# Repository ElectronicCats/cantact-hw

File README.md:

# CANtact Hardware

<p align="center">

</p>

<p align=center>
    Available at distributors:
 </p>
<p align=center>
  
</p>

<p align=center>

</p>

CANtact is a low-cost, open-source CAN bus interface hardware design, designed specifically for automotive diagnostics, industrial automation, and embedded systems development.

CANtact is a high-end CAN bus interface tool based on the original CANtact design, with optimization focused in rough order on (1) reliability, (2) ease of use, (3) cost-effectiveness, and finally (4) expandability. This results in a tool that covers many automotive and industrial use-cases, making it accessible for hobbyists and professionals alike.

As an open-source project and as a remix of the original CANtact design, it also collects inputs from various community members, and welcomes your contributions!

### FEATURES AVAILABLE ⚡🚗

* USB C, RJ45 and OBDII
* Low-cost design with open-source hardware files.
* 3D printable case files included.
* Compatible with popular CAN analysis software.
* Easy assembly with clear documentation.

## Thanks / Contributors

CANtact Hardware is a community-focused project, with major contributions from:

* Original CANtact design team
* ElectronicCats team (KiCad port, improvements, and variants)
* KiCad community for excellent open-source PCB design tools
* Open-source hardware community

### Useful References

If you don't know where to start with CAN bus communication, you may find automotive diagnostic resources and CAN bus protocol documentation useful.

You can see examples of CANtact being used in automotive diagnostics and industrial applications.

**WARNING**: Always ensure proper CAN bus termination and follow safety guidelines when working with automotive systems. Do NOT connect to live automotive systems without proper isolation.

## How to contribute 

Contributions are welcome!

Please read the document [**Contribution manual**](https://github.com/ElectronicCats/electroniccats-cla/blob/main/electroniccats-contribution-manual.md) which will show you how to contribute your changes to the project.

✨ Thanks to all our [Contributors](https://github.com/ElectronicCats/Minino/graphs/contributors)! ✨ ✨

See [**_Electronic Cats CLA_**](https://github.com/ElectronicCats/electroniccats-cla/blob/main/electroniccats-cla.md) for more information.

See the [**Community code of conduct**](https://github.com/ElectronicCats/electroniccats-cla/blob/main/electroniccats-community-code-of-conduct.md) for a vision of the community we want to build and what we expect from it.

## 3D Printed Case

Custom 3D printable case files are included in the `case/` directory:
- `CANTAC_case_top.stl` - Top cover
- `CANTAC_case_bttm.stl` - Bottom cover

## Documentation

- **Official Documentation**: [Linklayer Wiki](https://cantact.io/cantact/users-guide.html)

## Where to Buy

Ready-made CANtact devices are available from:

- 🇺🇸 [Hacker Warehouse](https://hackerwarehouse.com) (USA)

## License

This project CANtact Hardware is adapted from the original CANtact design and is licensed under CC BY-SA 4.0, "CANtact Hardware" contains modifications such as: porting the project to KiCad, modifying BOM and dimensions, and adding new variants, is licensed under CC BY-SA 4.0 by ElectronicCats.

Electronic Cats invests time and resources in providing this open-source design. Please support Electronic Cats and open-source hardware by purchasing products from Electronic Cats!

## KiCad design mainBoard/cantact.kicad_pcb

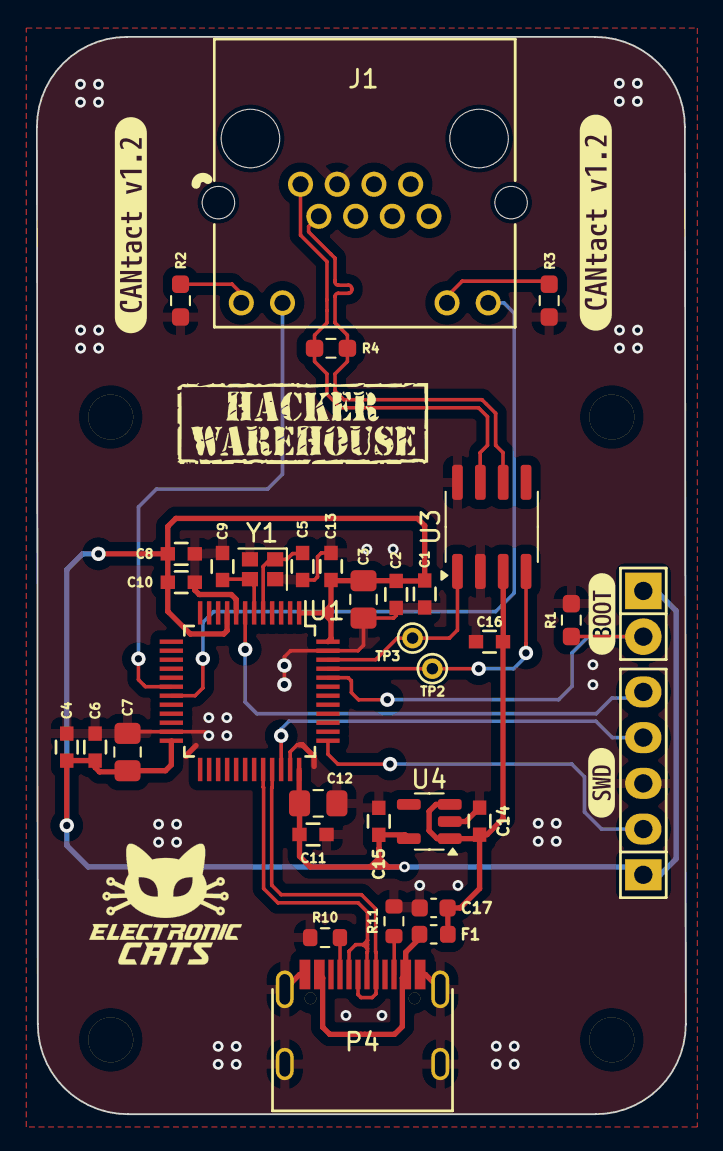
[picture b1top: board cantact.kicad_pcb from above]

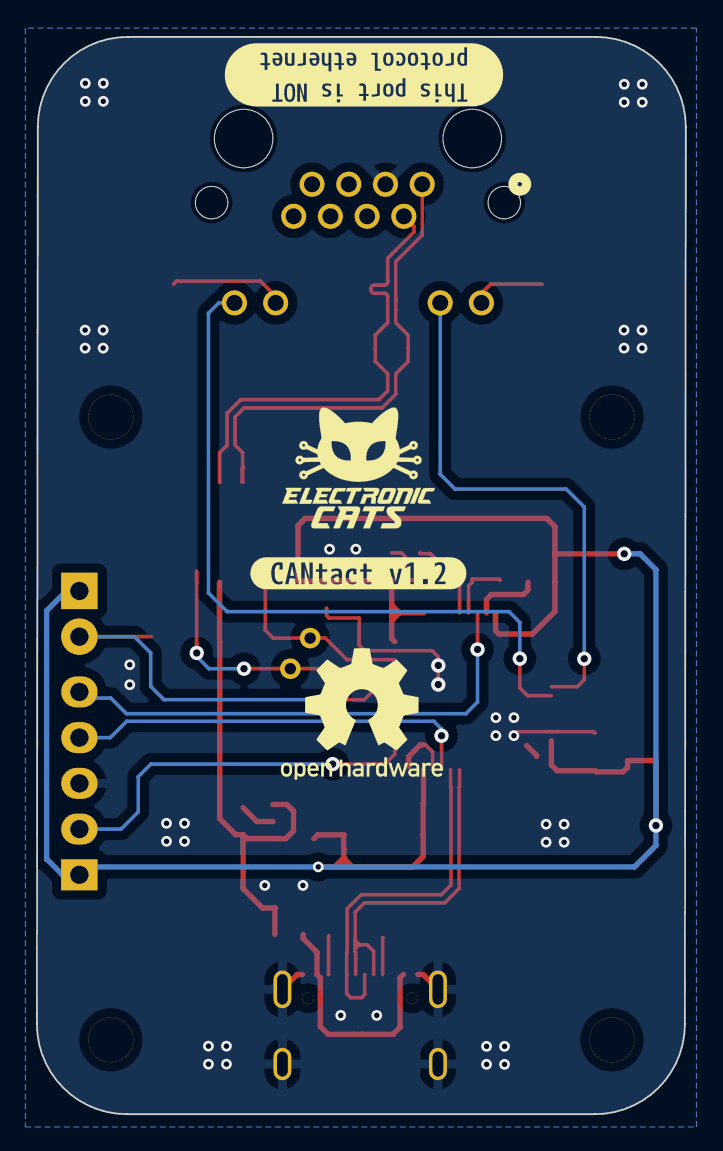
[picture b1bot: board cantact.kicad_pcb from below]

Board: 2 copper layers, 36.1 x 59.9 mm, 40 parts (2 on the bottom side), 22 nets.

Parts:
C1, C2, C4, C6, C11, C13, C16: 0.1uF; C_0603
C3, C7, C12: 4.7uF; C_0805_2012Metric_Pad1.18x1.45mm_HandSolder
C5, C9: 18pF; C_0603
C8: 10nF; C_0603
C10, C14, C15: 1uF; C_0603
C17: 10uF; C_0603_1608Metric
F1: 750mA; Fuse_0603_1608Metric
J1: Cantact; CONN12_R-RJ45_CKM
JP1: Boot Mode; Pin_Header_Straight_1x02
P2: SWD; Pin_Header_Straight_1x05
P4: USB_C_Plug_USB2.0; C393939
R1: 510; R_0603_1608Metric_Pad0.98x0.95mm_HandSolder
R2, R3, R4: 120; R_0603_1608Metric_Pad0.98x0.95mm_HandSolder
R10, R11: 5k1; R_0603_1608Metric
TP2, TP3: TST; PINTST
U1: STM32F042C6T6; LQFP-48_7x7mm_Pitch0.5mm
U3: MCP2551-I/SN; SOIC-8_3.9x4.9mm_P1.27mm
U4: XC6220B331MR-G; SOT-23-5
Y1: 16 Mhz; Crystal_SMD_2016-4Pin_2.0x1.6mm
kibuzzard-68FBEE71: G***; kibuzzard-68FBEE71
kibuzzard-68FBEEA6: G***; kibuzzard-68FBEEA6
kibuzzard-68FFF3A1: G***; kibuzzard-68FFF3A1
kibuzzard-68FFF3A9: G***; kibuzzard-68FFF3A9
kibuzzard-68FFF3B2: G***; kibuzzard-68FFF3B2
kibuzzard-68FFF13A: G***; kibuzzard-68FFF13A

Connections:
+3V3: C1.1, C2.1, C3.1, C4.1, C6.1, C7.1, C8.1, C10.1, C11.1, C12.1, C13.1, C15.1, JP1.1, P2.1, U1.1 (VBAT), U1.9 (VDDA), U1.24 (VDD), U1.36 (VDDIO), U1.48 (VDD), U4.5 (VOUT)
+5V: C14.1, C16.2, C17.1, F1.2, U3.3 (VDD), U4.1 (VIN), U4.3 (EN)
/CAN+: J1.1, R4.2, U3.7 (CANH)
/CAN-: J1.2, R4.1, U3.6 (CANL)
/CAN_RX: TP2.1, U1.45 (PB8), U3.4 (RXD)
/CAN_TX: TP3.1, U1.46 (PB9), U3.1 (TXD)
/D+: P4.A6 (D+), U1.33 (PA12)
/D-: P4.A7 (D-), U1.32 (PA11)
/LED_GREEN: J1.11, U1.18 (PB0)
/LED_RED: J1.9, U1.19 (PB1)
/NRST: P2.5, U1.7 (NRST)
/SWCLK: P2.2, U1.37 (PA14)
/SWDIO: P2.4, U1.34 (PA13)
GND: C1.2, C2.2, C3.2, C4.2, C5.2, C6.2, C7.2, C8.2, C9.2, C10.2, C11.2, C12.2, C13.2, C14.2, C15.2, C16.1, C17.2, J1.3, P2.3, P4.A1 (GND), P4.S1 (SHIELD), R1.2, R2.2, R3.2, R10.1, R11.1, U1.8 (VSSA), U1.23 (VSS), U1.35 (VSS), U1.47 (VSS), U3.2 (VSS), U3.8 (Rs), U4.2 (GND), Y1.2, Y1.4
unnamed: F1.1, P4.A4 (VBUS)
unnamed: J1.10, R3.1
unnamed: J1.12, R2.1
unnamed: JP1.2, R1.1, U1.44 (BOOT0-PF11)
unnamed: P4.A5 (CC), R10.2
unnamed: P4.B5 (VCONN), R11.2
unnamed: C5.1, U1.5 (PF0-OSC_IN), Y1.1
unnamed: C9.1, U1.6 (PF1-OSC_OUT), Y1.3

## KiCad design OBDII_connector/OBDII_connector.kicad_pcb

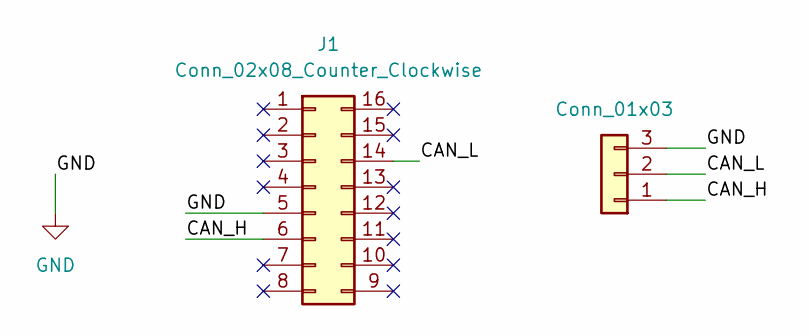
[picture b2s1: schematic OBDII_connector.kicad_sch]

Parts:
J1: Conn_02x08_Counter_Clockwise; OBD-II-Sparkfun v2.0
J3: Conn_01x03; PinHeader_1x03_P2.54mm_Vertical; LCSC# C541850

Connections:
/CAN_H: J1.6, J3.1
/CAN_L: J1.14, J3.2
GND: J1.5, J3.3

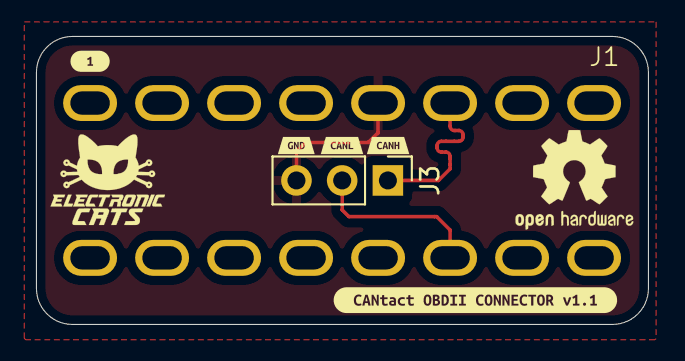
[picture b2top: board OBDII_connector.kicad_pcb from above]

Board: 2 copper layers, 34.0 x 16.0 mm, 7 parts (0 on the bottom side), 3 nets.

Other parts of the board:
kibuzzard-66AA65D6: G***; kibuzzard-66AA65D6
kibuzzard-67DDAD0A: G***; kibuzzard-67DDAD0A
kibuzzard-67DDAD2E: G***; kibuzzard-67DDAD2E
kibuzzard-67DDAD71: G***; kibuzzard-67DDAD71
kibuzzard-67FE8BBD: G***; kibuzzard-67FE8BBD

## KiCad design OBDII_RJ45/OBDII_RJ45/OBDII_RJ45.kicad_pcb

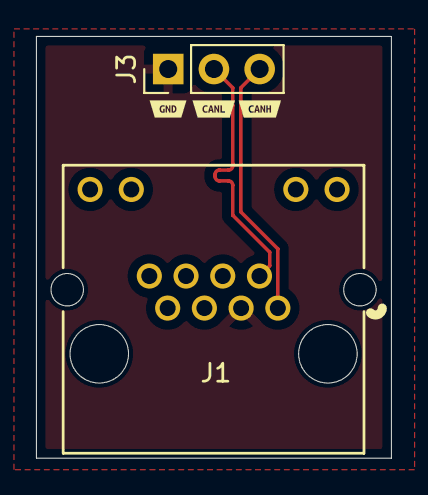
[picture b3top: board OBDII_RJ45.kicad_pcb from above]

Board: 2 copper layers, 19.7 x 23.4 mm, 6 parts (1 on the bottom side), 3 nets.

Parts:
J1: RJ45; CONN12_R-RJ45_CKM
J3: Conn_01x03; PinHeader_1x03_P2.54mm_Vertical
kibuzzard-67DDB05E: G***; kibuzzard-67DDB05E
kibuzzard-67DDB06D: G***; kibuzzard-67DDB06D
kibuzzard-67DDB066: G***; kibuzzard-67DDB066
kibuzzard-67FE8E6B: G***; kibuzzard-67FE8E6B

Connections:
/CAN+: J1.1, J3.3
/CAN-: J1.2, J3.2
GND: J1.3, J3.1

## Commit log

2025-03-12 feat: rewire missing simbols
2025-03-12 feat: update project to kicad 9
2025-03-12 feat(hw): schematic & pcb updated
2025-03-14 feat: replace USB & RJ45 ports
2025-03-18 refactor(hw): PCB routing
2025-03-18 refactor(hw): tracks & vias size
2025-03-19 refactor(hw): crystal position on PCB
2025-03-21 feat: add GND between OBDII connector & OBDII_RJ45
2025-03-21 feat(hw): add lcsc parts
2025-03-28 feat(hw): move differential pair of CANH and CANL
2025-03-28 feat(hw): update pcb
2025-03-28 refactor: 3v net & change usb resistors to front layer
2025-04-15 feat(Hw):Update_Labels
2025-04-18 Fix: CANbus routing and added 3D models
2025-04-18 fix(hw): update labels
2025-04-21 Fix: CANbus routing for OBDII_RJ45
2025-10-23 feat(hw): add 3d files for housing
2025-10-24 fix(hw): correct STL export units
2025-10-24 feat: new paths
2025-10-24 docs: update README
2025-10-24 feat(Hw):Update_Route_And_Labels
2025-10-24 feat(Hw):Update_Route
2025-10-27 feat(Hw):Update_Labels_And_BOM
2025-10-27 feat: logo adjust
2025-10-27 feat:update v1.2
2025-10-30 fix: change footprint
2026-05-06 To update ReadME
    Updated README with new images, contribution guidelines, and links.
